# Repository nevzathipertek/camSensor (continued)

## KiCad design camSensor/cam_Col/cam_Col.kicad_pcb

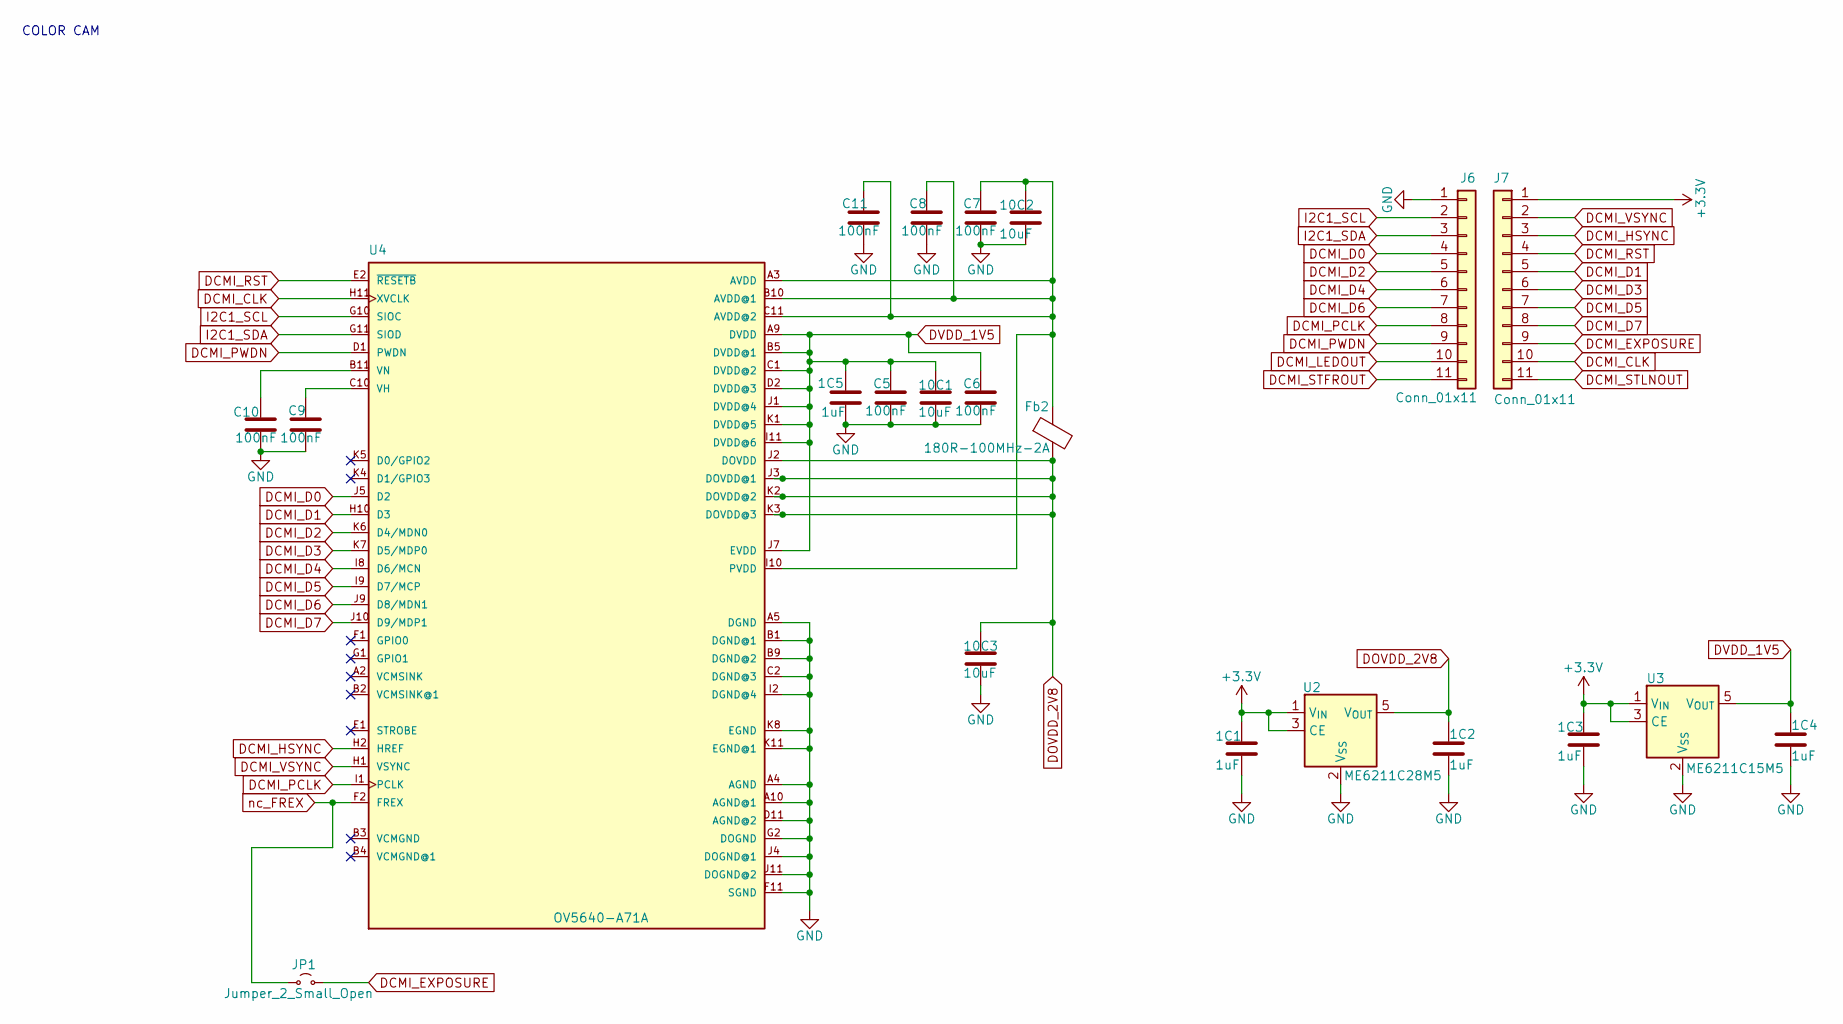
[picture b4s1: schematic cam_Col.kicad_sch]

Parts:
1C1, 1C2, 1C3, 1C4, 1C5: 1uF; C_0603_1608Metric
10C1, 10C2, 10C3: 10uF; C_0603_1608Metric
C5, C6, C7, C8, C9, C10, C11: 100nF; C_0603_1608Metric
Fb2: 180R-100MHz-2A; L_0805_2012Metric
J6, J7: Conn_01x11; PinHeader_1x11_P2.54mm_Vertical
JP1: Jumper_2_Small_Open; SolderJumper-2_P1.3mm_Open_RoundedPad1.0x1.5mm
U2: ME6211C28M5; SOT-23-5
U3: ME6211C15M5; SOT-23-5
U4: OV5640-A71A; BGA71C50P11X11_598X584X81

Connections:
+3.3V: 1C1.1, 1C3.1, J7.1, U2.1 (V_{IN}), U2.3 (CE), U3.1 (V_{IN}), U3.3 (CE)
DCMI_CLK: J7.10, U4.H11 (XVCLK)
DCMI_D0: J6.4, U4.J5 (D2)
DCMI_D1: J7.5, U4.H10 (D3)
DCMI_D2: J6.5, U4.K6 (D4/MDN0)
DCMI_D3: J7.6, U4.K7 (D5/MDP0)
DCMI_D4: J6.6, U4.I8 (D6/MCN)
DCMI_D5: J7.7, U4.I9 (D7/MCP)
DCMI_D6: J6.7, U4.J9 (D8/MDN1)
DCMI_D7: J7.8, U4.J10 (D9/MDP1)
DCMI_EXPOSURE: J7.9, JP1.2 (B)
DCMI_HSYNC: J7.3, U4.H2 (HREF)
DCMI_LEDOUT: J6.10
DCMI_PCLK: J6.8, U4.I1 (PCLK)
DCMI_PWDN: J6.9, U4.D1 (PWDN)
DCMI_RST: J7.4, U4.E2 (~RESETB)
DCMI_STFROUT: J6.11
DCMI_STLNOUT: J7.11
DCMI_VSYNC: J7.2, U4.H1 (VSYNC)
DOVDD_2V8: 1C2.1, 10C3.1, Fb2.2, U2.5 (V_{OUT}), U4.J2 (DOVDD), U4.J3 (DOVDD@1), U4.K2 (DOVDD@2), U4.K3 (DOVDD@3)
DVDD_1V5: 1C4.1, 1C5.1, 10C1.1, C5.1, C6.1, U3.5 (V_{OUT}), U4.A9 (DVDD), U4.B5 (DVDD@1), U4.C1 (DVDD@2), U4.D2 (DVDD@3), U4.I11 (DVDD@6), U4.J1 (DVDD@4), U4.J7 (EVDD), U4.K1 (DVDD@5)
GND: 1C1.2, 1C2.2, 1C3.2, 1C4.2, 1C5.2, 10C1.2, 10C2.2, 10C3.2, C5.2, C6.2, C7.2, C8.2, C9.2, C10.2, C11.2, J6.1, U2.2 (V_{SS}), U3.2 (V_{SS}), U4.A4 (AGND), U4.A5 (DGND), U4.A10 (AGND@1), U4.B1 (DGND@1), U4.B9 (DGND@2), U4.C2 (DGND@3), U4.D11 (AGND@2), U4.F11 (SGND), U4.G2 (DOGND), U4.I2 (DGND@4), U4.J4 (DOGND@1), U4.J11 (DOGND@2), U4.K8 (EGND), U4.K11 (EGND@1)
I2C1_SCL: J6.2, U4.G10 (SIOC)
I2C1_SDA: J6.3, U4.G11 (SIOD)
unnamed: 10C2.1, C7.1, C8.1, C11.1, Fb2.1, U4.A3 (AVDD), U4.B10 (AVDD@1), U4.C11 (AVDD@2), U4.I10 (PVDD)
unnamed: C9.1, U4.C10 (VH)
unnamed: C10.1, U4.B11 (VN)
nc_FREX: JP1.1 (A), U4.F2 (FREX)

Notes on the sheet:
COLOR CAM

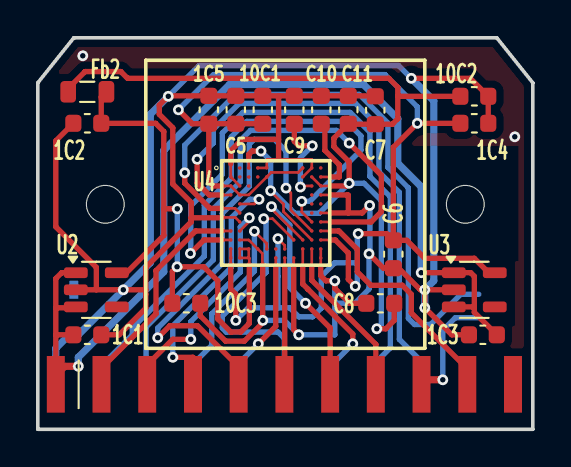
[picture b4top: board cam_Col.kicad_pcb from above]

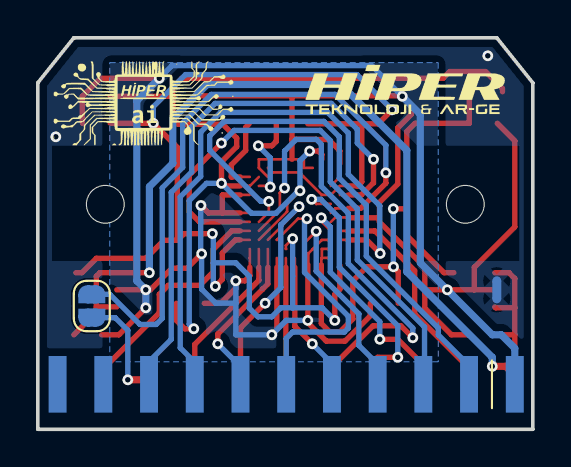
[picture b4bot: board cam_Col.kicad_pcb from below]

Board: 2 copper layers, 27.5 x 21.8 mm, 27 parts (5 on the bottom side), 26 nets.

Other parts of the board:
CMN1: EarthClean; NetTie-2_SMD_Pad0.5mm
H1, H2: MountingHole_2.1mm
ai: LOGO
hiper: LOGO

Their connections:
Earth_Clean: CMN1.1, CMN1.2

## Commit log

2025-02-13 version:01.01
